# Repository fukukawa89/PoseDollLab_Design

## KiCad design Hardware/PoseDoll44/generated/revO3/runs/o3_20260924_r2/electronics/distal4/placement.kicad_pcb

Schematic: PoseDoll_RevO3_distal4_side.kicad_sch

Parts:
C26, C27, C28, C29: 100n X7R; C_0603_1608Metric
C50: 1u X7R; C_0603_1608Metric
J16: P6 sensor / CS GPIO8; JST_SH_BM06B-SRSS-TB_1x06-1MP_P1.00mm_Vertical
J17: P7 sensor / CS GPIO9; JST_SH_BM06B-SRSS-TB_1x06-1MP_P1.00mm_Vertical
J18: P8 sensor / CS GPIO10; JST_SH_BM06B-SRSS-TB_1x06-1MP_P1.00mm_Vertical
J19: P9 sensor / CS GPIO14; JST_SH_BM06B-SRSS-TB_1x06-1MP_P1.00mm_Vertical
J50: SM14B-SRSS-TB / SHR-14V-S / SSH-003T-P0.2-H; JST_SH_SM14B-SRSS-TB_1x14-1MP_P1.00mm_Horizontal
R160, R161, R162, R170, R171, R172, R180, R181, R182, R190, R191, R192: 100R; R_0603_1608Metric
R163, R167, R173, R177, R183, R187, R193, R197: 10k; R_0603_1608Metric
R164, R165, R174, R175, R184, R185, R194, R195: 47k; R_0603_1608Metric
R166, R176, R186, R196: 100k; R_0603_1608Metric
R500: 100R return source damping candidate; R_0603_1608Metric
U16, U17, U18, U19: SN74LVC125ABQAR; DHWQFN-14-1EP_2.5x3mm_P0.5mm_EP1x1.5mm

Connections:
/+3V3: C26.1, C27.1, C28.1, C29.1, C50.1, J16.2, J17.2, J18.2, J19.2, J50.13, J50.14, R163.1, R167.1, R173.1, R177.1, R183.1, R187.1, R193.1, R197.1, U16.14 (VCC), U17.14 (VCC), U18.14 (VCC), U19.14 (VCC)
/CS6_REMOTE: J50.7, R163.2, U16.1 (1OE_N), U16.4 (2OE_N), U16.10 (3OE_N), U16.12 (4A)
/CS7_REMOTE: J50.8, R173.2, U17.1 (1OE_N), U17.4 (2OE_N), U17.10 (3OE_N), U17.12 (4A)
/CS8_REMOTE: J50.10, R183.2, U18.1 (1OE_N), U18.4 (2OE_N), U18.10 (3OE_N), U18.12 (4A)
/CS9_REMOTE: J50.11, R193.2, U19.1 (1OE_N), U19.4 (2OE_N), U19.10 (3OE_N), U19.12 (4A)
/GND: C26.2, C27.2, C28.2, C29.2, C50.2, J16.1, J17.1, J18.1, J19.1, J50.1, J50.3, J50.5, J50.9, J50.12, R164.2, R165.2, R166.2, R174.2, R175.2, R176.2, R184.2, R185.2, R186.2, R194.2, R195.2, R196.2, U16.7 (GND), U16.13 (4OE_N), U16.15 (EP_GND), U17.7 (GND), U17.13 (4OE_N), U17.15 (EP_GND), U18.7 (GND), U18.13 (4OE_N), U18.15 (EP_GND), U19.7 (GND), U19.13 (4OE_N), U19.15 (EP_GND)
/LINK_MISO: J50.6, R500.2
/LINK_MOSI: J50.4, U16.5 (2A), U17.5 (2A), U18.5 (2A), U19.5 (2A)
/LINK_SCK: J50.2, U16.2 (1A), U17.2 (1A), U18.2 (1A), U19.2 (1A)
/MISO_REMOTE_DRV: R500.1, U16.8 (3Y), U17.8 (3Y), U18.8 (3Y), U19.8 (3Y)
/P6_CS: J16.6, R162.2, R167.2
/P6_CS_DRV: R162.1, U16.11 (4Y)
/P6_MISO: J16.5, R166.1, U16.9 (3A)
/P6_MOSI: J16.4, R161.2, R165.1
/P6_MOSI_DRV: R161.1, U16.6 (2Y)
/P6_SCK: J16.3, R160.2, R164.1
/P6_SCK_DRV: R160.1, U16.3 (1Y)
/P7_CS: J17.6, R172.2, R177.2
/P7_CS_DRV: R172.1, U17.11 (4Y)
/P7_MISO: J17.5, R176.1, U17.9 (3A)
/P7_MOSI: J17.4, R171.2, R175.1
/P7_MOSI_DRV: R171.1, U17.6 (2Y)
/P7_SCK: J17.3, R170.2, R174.1
/P7_SCK_DRV: R170.1, U17.3 (1Y)
/P8_CS: J18.6, R182.2, R187.2
/P8_CS_DRV: R182.1, U18.11 (4Y)
/P8_MISO: J18.5, R186.1, U18.9 (3A)
/P8_MOSI: J18.4, R181.2, R185.1
/P8_MOSI_DRV: R181.1, U18.6 (2Y)
/P8_SCK: J18.3, R180.2, R184.1
/P8_SCK_DRV: R180.1, U18.3 (1Y)
/P9_CS: J19.6, R192.2, R197.2
/P9_CS_DRV: R192.1, U19.11 (4Y)
/P9_MISO: J19.5, R196.1, U19.9 (3A)
/P9_MOSI: J19.4, R191.2, R195.1
/P9_MOSI_DRV: R191.1, U19.6 (2Y)
/P9_SCK: J19.3, R190.2, R194.1
/P9_SCK_DRV: R190.1, U19.3 (1Y)

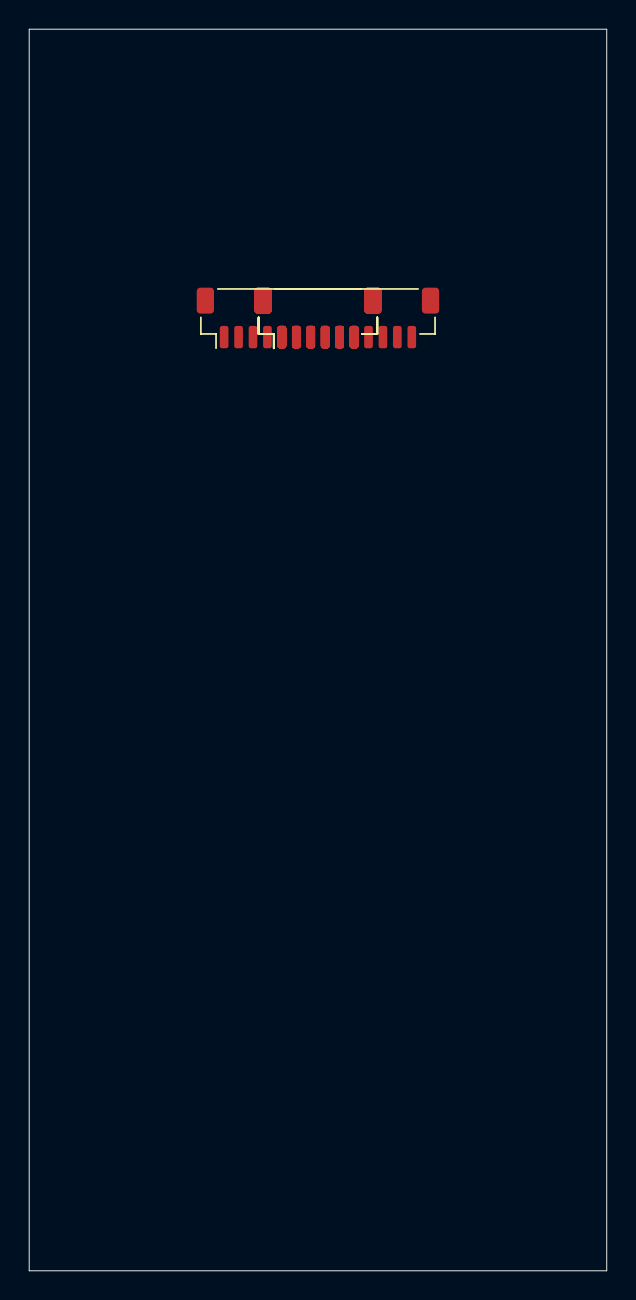
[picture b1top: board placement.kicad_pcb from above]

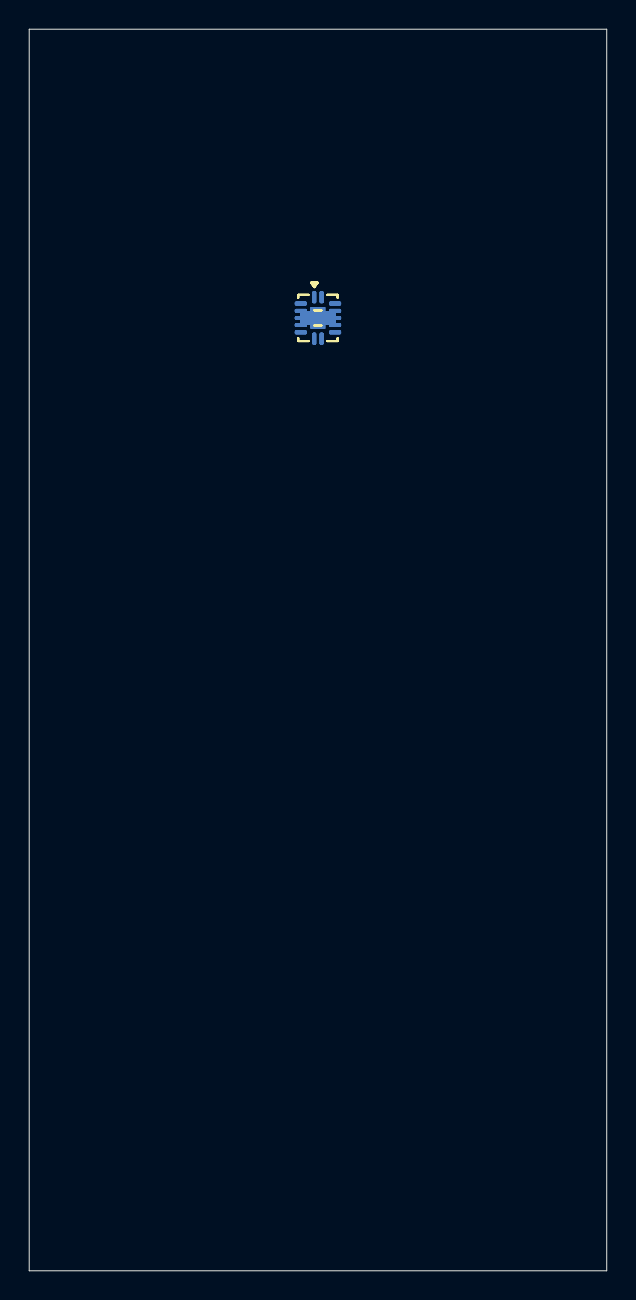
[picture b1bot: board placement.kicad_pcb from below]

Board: 4 copper layers, 40.0 x 86.0 mm, 47 parts (42 on the bottom side), 38 nets, no tracks yet.

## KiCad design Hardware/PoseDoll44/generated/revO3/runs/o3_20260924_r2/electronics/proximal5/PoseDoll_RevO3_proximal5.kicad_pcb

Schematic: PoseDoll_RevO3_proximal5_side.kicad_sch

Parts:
C1: 10u X5R 25V / CL21A106KAYNNNE; C_0805_2012Metric
C2, C4: 22u X5R 16V / CL21A226MOYNNNE; C_0805_2012Metric
C3, C5, C7, C21, C22, C23, C24, C25, C50, C51: 100n X7R; C_0603_1608Metric
C6: 1u X7R; C_0603_1608Metric
D1: PESD5V0S2BT,215; SOT-23
J1: 5V protected N3/N4 branch; not 12V qualified; JST_PH_B2B-PH-SM4-TB_1x02-1MP_P2.00mm_Vertical
J2: CAN IN / GND-L-H; JST_GH_BM03B-GHS-TBT_1x03-1MP_P1.25mm_Vertical
J3: CAN OUT / GND-L-H; JST_GH_BM03B-GHS-TBT_1x03-1MP_P1.25mm_Vertical
J11: P1 sensor / CS GPIO2; JST_SH_BM06B-SRSS-TB_1x06-1MP_P1.00mm_Vertical
J12: P2 sensor / CS GPIO4; JST_SH_BM06B-SRSS-TB_1x06-1MP_P1.00mm_Vertical
J13: P3 sensor / CS GPIO5; JST_SH_BM06B-SRSS-TB_1x06-1MP_P1.00mm_Vertical
J14: P4 sensor / CS GPIO6; JST_SH_BM06B-SRSS-TB_1x06-1MP_P1.00mm_Vertical
J15: P5 sensor / CS GPIO7; JST_SH_BM06B-SRSS-TB_1x06-1MP_P1.00mm_Vertical
J50: SM14B-SRSS-TB / SHR-14V-S / SSH-003T-P0.2-H; JST_SH_SM14B-SRSS-TB_1x14-1MP_P1.00mm_Horizontal
JP1: CAN TERM: close endpoints only; SolderJumper-2_P1.3mm_Open_Pad1.0x1.5mm
L1: LSXND4040TKL2R2MDG / 2.2uH; L_Taiyo-Yuden_NR-40xx
R1, R2, R4, R113, R117, R123, R127, R133, R137, R143, R147, R153, R157, R526, R527, R528, R529: 10k; R_0603_1608Metric
R3, R116, R126, R136, R146, R156: 100k; R_0603_1608Metric
R5: 120R 1% 0.33W / CRCW0603120RFKEAHP; R_0603_1608Metric
R110, R111, R112, R120, R121, R122, R130, R131, R132, R140, R141, R142, R150, R151, R152: 100R; R_0603_1608Metric
R114, R115, R124, R125, R134, R135, R144, R145, R154, R155: 47k; R_0603_1608Metric
R500, R501, R502, R503, R510, R511: 100R source damping candidate; R_0603_1608Metric
R530: 0R option / direct tri-state return; R_0603_1608Metric
TP1: UART_TX; TestPoint_Pad_D1.0mm
TP2: UART_RX; TestPoint_Pad_D1.0mm
TP3: GND; TestPoint_Pad_D1.0mm
TP4: PG; TestPoint_Pad_D1.0mm
TP5: EN; TestPoint_Pad_D1.0mm
TP6: BOOT_N; TestPoint_Pad_D1.0mm
U1: ESP32-S3-WROOM-1-N8; ESP32-S3-WROOM-1
U2: TPS62162DSGR; Texas_DSG0008A_WSON-8-1EP_2x2mm_P0.5mm_EP0.9x1.6mm
U3: TCAN332DR; SOIC-8_3.9x4.9mm_P1.27mm
U11, U12, U13, U14, U15, U50, U51: SN74LVC125ABQAR; DHWQFN-14-1EP_2.5x3mm_P0.5mm_EP1x1.5mm

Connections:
/+3V3: C2.1, C4.1, C5.1, C7.1, C21.1, C22.1, C23.1, C24.1, C25.1, C50.1, C51.1, J11.2, J12.2, J13.2, J14.2, J15.2, J50.13, J50.14, L1.2, R1.1, R2.1, R3.1, R4.1, R113.1, R117.1, R123.1, R127.1, R133.1, R137.1, R143.1, R147.1, R153.1, R157.1, R526.1, R527.1, R528.1, R529.1, U1.2 (3V3), U2.6 (VOS), U3.3 (VCC), U11.14 (VCC), U12.14 (VCC), U13.14 (VCC), U14.14 (VCC), U15.14 (VCC), U50.14 (VCC), U51.10 (3OE_N), U51.13 (4OE_N), U51.14 (VCC)
/+5V_IN: C1.1, C3.1, J1.1, U2.2 (VIN), U2.3 (EN)
/BOOT_N: R2.2, TP6.1, U1.27 (IO0)
/CAN_H: D1.2 (CAN2), J2.3, J3.3, R5.1, U3.7 (CANH)
/CAN_L: D1.1 (CAN1), J2.2, J3.2, JP1.2 (B), U3.6 (CANL)
/CAN_RX: U1.11 (IO18), U3.4 (RXD)
/CAN_TX: R4.2, U1.10 (IO17), U3.1 (TXD)
/CS1_MCU: R113.2, U1.38 (IO2), U11.1 (1OE_N), U11.4 (2OE_N), U11.10 (3OE_N), U11.12 (4A)
/CS2_MCU: R123.2, U1.4 (IO4), U12.1 (1OE_N), U12.4 (2OE_N), U12.10 (3OE_N), U12.12 (4A)
/CS3_MCU: R133.2, U1.5 (IO5), U13.1 (1OE_N), U13.4 (2OE_N), U13.10 (3OE_N), U13.12 (4A)
/CS4_MCU: R143.2, U1.6 (IO6), U14.1 (1OE_N), U14.4 (2OE_N), U14.10 (3OE_N), U14.12 (4A)
/CS5_MCU: R153.2, U1.7 (IO7), U15.1 (1OE_N), U15.4 (2OE_N), U15.10 (3OE_N), U15.12 (4A)
/CS6_MCU: R526.2, U1.12 (IO8), U50.9 (3A)
/CS6_REMOTE: J50.7, R502.2
/CS6_REMOTE_DRV: R502.1, U50.8 (3Y)
/CS7_MCU: R527.2, U1.17 (IO9), U50.12 (4A)
/CS7_REMOTE: J50.8, R503.2
/CS7_REMOTE_DRV: R503.1, U50.11 (4Y)
/CS8_MCU: R528.2, U1.18 (IO10), U51.2 (1A)
/CS8_REMOTE: J50.10, R510.2
/CS8_REMOTE_DRV: R510.1, U51.3 (1Y)
/CS9_MCU: R529.2, U1.22 (IO14), U51.5 (2A)
/CS9_REMOTE: J50.11, R511.2
/CS9_REMOTE_DRV: R511.1, U51.6 (2Y)
/EN: C6.1, R1.2, TP5.1, U1.3 (EN)
/GND: C1.2, C2.2, C3.2, C4.2, C5.2, C6.2, C7.2, C21.2, C22.2, C23.2, C24.2, C25.2, C50.2, C51.2, D1.3 (GND), J1.2, J2.1, J3.1, J11.1, J12.1, J13.1, J14.1, J15.1, J50.1, J50.3, J50.5, J50.9, J50.12, R114.2, R115.2, R116.2, R124.2, R125.2, R126.2, R134.2, R135.2, R136.2, R144.2, R145.2, R146.2, R154.2, R155.2, R156.2, TP3.1, U1.1 (GND), U1.40 (GND), U1.41 (GND), U2.1 (PGND), U2.4 (AGND), U2.5 (FB), U2.9 (PAD), U3.2 (GND), U11.7 (GND), U11.13 (4OE_N), U11.15 (EP_GND), U12.7 (GND), U12.13 (4OE_N), U12.15 (EP_GND), U13.7 (GND), U13.13 (4OE_N), U13.15 (EP_GND), U14.7 (GND), U14.13 (4OE_N), U14.15 (EP_GND), U15.7 (GND), U15.13 (4OE_N), U15.15 (EP_GND), U50.1 (1OE_N), U50.4 (2OE_N), U50.7 (GND), U50.10 (3OE_N), U50.13 (4OE_N), U50.15 (EP_GND), U51.1 (1OE_N), U51.4 (2OE_N), U51.7 (GND), U51.9 (3A), U51.12 (4A), U51.15 (EP_GND)
/LINK_MISO: J50.6, R530.1
/LINK_MOSI: J50.4, R501.2
/LINK_MOSI_DRV: R501.1, U50.6 (2Y)
/LINK_SCK: J50.2, R500.2
/LINK_SCK_DRV: R500.1, U50.3 (1Y)
/P1_CS: J11.6, R112.2, R117.2
/P1_CS_DRV: R112.1, U11.11 (4Y)
/P1_MISO: J11.5, R116.1, U11.9 (3A)
/P1_MOSI: J11.4, R111.2, R115.1
/P1_MOSI_DRV: R111.1, U11.6 (2Y)
/P1_SCK: J11.3, R110.2, R114.1
/P1_SCK_DRV: R110.1, U11.3 (1Y)
/P2_CS: J12.6, R122.2, R127.2
/P2_CS_DRV: R122.1, U12.11 (4Y)
/P2_MISO: J12.5, R126.1, U12.9 (3A)
/P2_MOSI: J12.4, R121.2, R125.1
/P2_MOSI_DRV: R121.1, U12.6 (2Y)
/P2_SCK: J12.3, R120.2, R124.1
/P2_SCK_DRV: R120.1, U12.3 (1Y)
/P3_CS: J13.6, R132.2, R137.2
/P3_CS_DRV: R132.1, U13.11 (4Y)
/P3_MISO: J13.5, R136.1, U13.9 (3A)
/P3_MOSI: J13.4, R131.2, R135.1
/P3_MOSI_DRV: R131.1, U13.6 (2Y)
/P3_SCK: J13.3, R130.2, R134.1
/P3_SCK_DRV: R130.1, U13.3 (1Y)
/P4_CS: J14.6, R142.2, R147.2
/P4_CS_DRV: R142.1, U14.11 (4Y)
/P4_MISO: J14.5, R146.1, U14.9 (3A)
/P4_MOSI: J14.4, R141.2, R145.1
/P4_MOSI_DRV: R141.1, U14.6 (2Y)
/P4_SCK: J14.3, R140.2, R144.1
/P4_SCK_DRV: R140.1, U14.3 (1Y)
/P5_CS: J15.6, R152.2, R157.2
/P5_CS_DRV: R152.1, U15.11 (4Y)
/P5_MISO: J15.5, R156.1, U15.9 (3A)
/P5_MOSI: J15.4, R151.2, R155.1
/P5_MOSI_DRV: R151.1, U15.6 (2Y)
/P5_SCK: J15.3, R150.2, R154.1
/P5_SCK_DRV: R150.1, U15.3 (1Y)
/PG: R3.2, TP4.1, U2.8 (PG)
/SPI_MISO: R530.2, U1.21 (IO13), U11.8 (3Y), U12.8 (3Y), U13.8 (3Y), U14.8 (3Y), U15.8 (3Y)
/SPI_MOSI: U1.19 (IO11), U11.5 (2A), U12.5 (2A), U13.5 (2A), U14.5 (2A), U15.5 (2A), U50.5 (2A)
/SPI_SCK: U1.20 (IO12), U11.2 (1A), U12.2 (1A), U13.2 (1A), U14.2 (1A), U15.2 (1A), U50.2 (1A)
/SW_BUCK: L1.1, U2.7 (SW)
/TERM_R: JP1.1 (A), R5.2
/UART_RX: TP2.1, U1.36 (RXD0)
/UART_TX: TP1.1, U1.37 (TXD0)

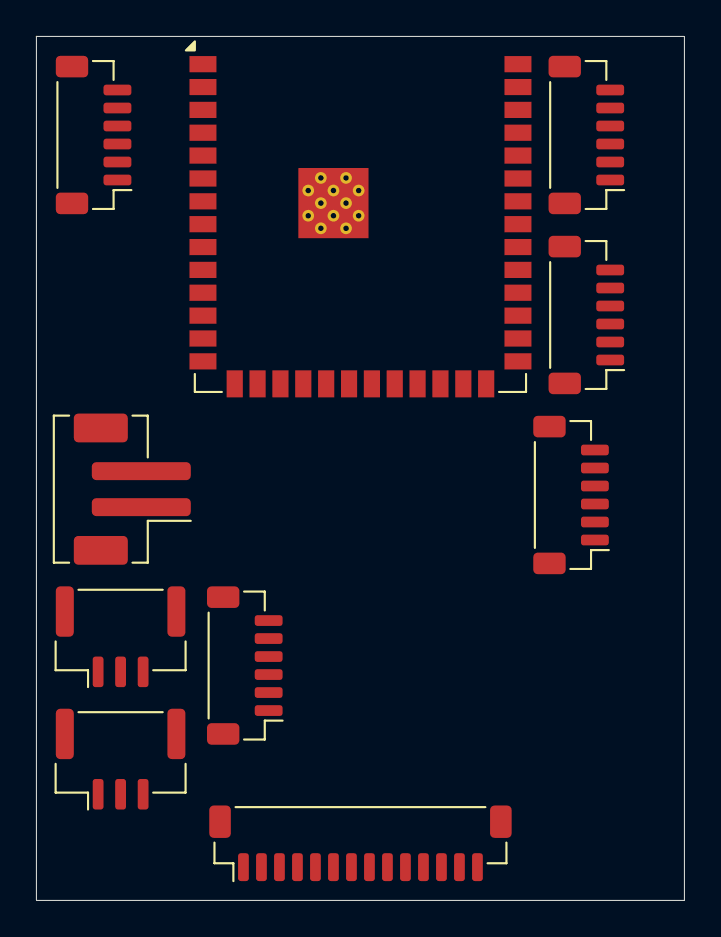
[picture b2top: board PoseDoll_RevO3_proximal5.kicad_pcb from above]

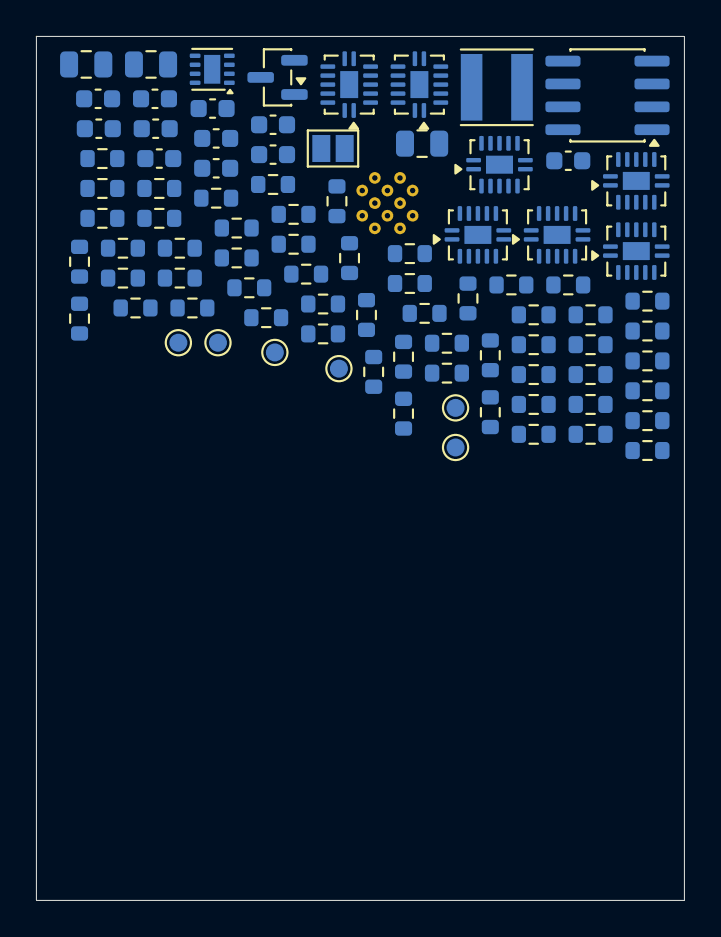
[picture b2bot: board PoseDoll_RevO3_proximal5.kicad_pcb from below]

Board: 4 copper layers, 36.0 x 48.0 mm, 98 parts (88 on the bottom side), 74 nets, no tracks yet.
